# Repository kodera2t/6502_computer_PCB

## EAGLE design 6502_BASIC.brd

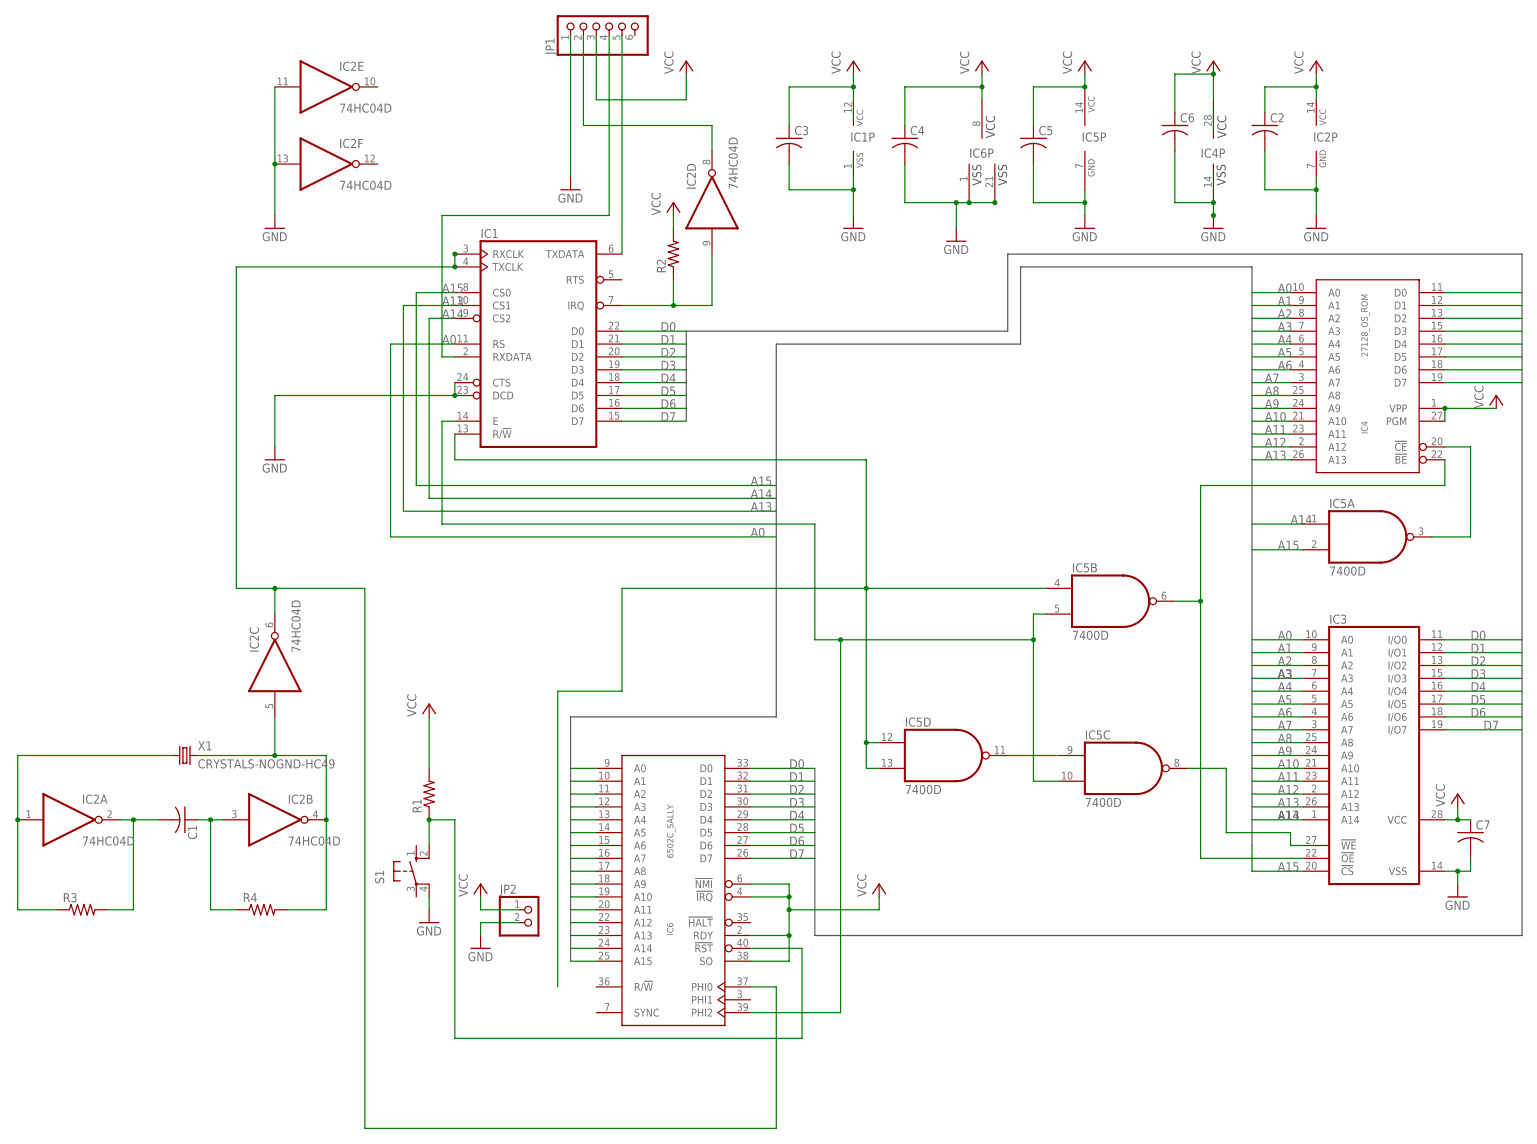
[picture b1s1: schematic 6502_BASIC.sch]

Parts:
C1, C2, C3, C4, C5, C6, C7: C-USC1608; C1608
IC1: 6850; DIL24
IC2: 74HC04D; SO14
IC3: 62256P; DIL28-6
IC4: 27128_OS_ROM; DIL28
IC5: 7400D; SO14
IC6: 6502C_SALLY; DIL40
JP1: HEADER-1X6; 1X06_OVAL
JP2: HEADER-1X2; 1X02_OVAL
R1, R2, R3, R4: R-US_R0603; R0603
S1: 10-XX; B3F-10XX
X1: CRYSTALS-NOGND-HC49; HC49

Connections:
A0: IC1.11 (RS), IC3.10 (A0), IC4.10 (A0), IC6.9 (A0)
A1: IC3.9 (A1), IC4.9 (A1), IC6.10 (A1)
A2: IC3.8 (A2), IC4.8 (A2), IC6.11 (A2)
A3: IC3.7 (A3), IC4.7 (A3), IC6.12 (A3)
A4: IC3.6 (A4), IC4.6 (A4), IC6.13 (A4)
A5: IC3.5 (A5), IC4.5 (A5), IC6.14 (A5)
A6: IC3.4 (A6), IC4.4 (A6), IC6.15 (A6)
A7: IC3.3 (A7), IC4.3 (A7), IC6.16 (A7)
A8: IC3.25 (A8), IC4.25 (A8), IC6.17 (A8)
A9: IC3.24 (A9), IC4.24 (A9), IC6.18 (A9)
A10: IC3.21 (A10), IC4.21 (A10), IC6.19 (A10)
A11: IC3.23 (A11), IC4.23 (A11), IC6.20 (A11)
A12: IC3.2 (A12), IC4.2 (A12), IC6.22 (A12)
A13: IC1.10 (CS1), IC3.26 (A13), IC4.26 (A13), IC6.23 (A13)
A14: IC1.9 (CS2), IC3.1 (A14), IC5.1 (I0), IC6.24 (A14)
A15: IC1.8 (CS0), IC3.20 (!CS), IC5.2 (I1), IC6.25 (A15)
D0: IC1.22 (D0), IC3.11 (I/O0), IC4.11 (D0), IC6.33 (D0)
D1: IC1.21 (D1), IC3.12 (I/O1), IC4.12 (D1), IC6.32 (D1)
D2: IC1.20 (D2), IC3.13 (I/O2), IC4.13 (D2), IC6.31 (D2)
D3: IC1.19 (D3), IC3.15 (I/O3), IC4.15 (D3), IC6.30 (D3)
D4: IC1.18 (D4), IC3.16 (I/O4), IC4.16 (D4), IC6.29 (D4)
D5: IC1.17 (D5), IC3.17 (I/O5), IC4.17 (D5), IC6.28 (D5)
D6: IC1.16 (D6), IC3.18 (I/O6), IC4.18 (D6), IC6.27 (D6)
D7: IC1.15 (D7), IC3.19 (I/O7), IC4.19 (D7), IC6.26 (D7)
GND: C2.2, C3.2, C4.2, C5.2, C6.2, C7.2, IC1.1 (VSS), IC1.23 (DCD), IC1.24 (CTS), IC2.7 (GND), IC2.11 (I), IC2.13 (I), IC3.14 (VSS), IC4.14 (VSS), IC5.7 (GND), IC6.1 (VSS), IC6.21 (VSS1), JP1.1, JP2.2, S1.4 (P1)
unnamed: IC3.27 (!WE), IC5.8 (O)
unnamed: IC3.22 (!OE), IC4.22 (!BE), IC5.6 (O)
unnamed: IC1.3 (RXCLK), IC1.4 (TXCLK), IC2.6 (O), IC6.37 (PHI0)
unnamed: IC5.9 (I0), IC5.11 (O)
unnamed: IC4.20 (!CE), IC5.3 (O)
unnamed: IC1.14 (E), IC5.5 (I1), IC5.10 (I1), IC6.39 (PHI2)
unnamed: IC1.13 (R/!W), IC5.4 (I0), IC5.12 (I0), IC5.13 (I1)
unnamed: IC2.4 (O), IC2.5 (I), R4.2, X1.2
unnamed: IC1.7 (IRQ), IC2.9 (I), R2.1
unnamed: IC2.8 (O), JP1.2
unnamed: C1.1, IC2.3 (I), R4.1
unnamed: IC6.40 (!RST), R1.1, S1.2 (S1)
unnamed: C1.2, IC2.2 (O), R3.2
unnamed: IC2.1 (I), R3.1, X1.1
unnamed: IC1.6 (TXDATA), JP1.5
unnamed: IC1.2 (RXDATA), JP1.4
VCC: C2.1, C3.1, C4.1, C5.1, C6.1, C7.1, IC1.12 (VCC), IC2.14 (VCC), IC3.28 (VCC), IC4.1 (VPP), IC4.27 (PGM), IC4.28 (VCC), IC5.14 (VCC), IC6.2 (RDY), IC6.4 (!IRQ), IC6.6 (!NMI), IC6.8 (VCC), IC6.38 (SO), JP1.3, JP2.1, R1.2, R2.2

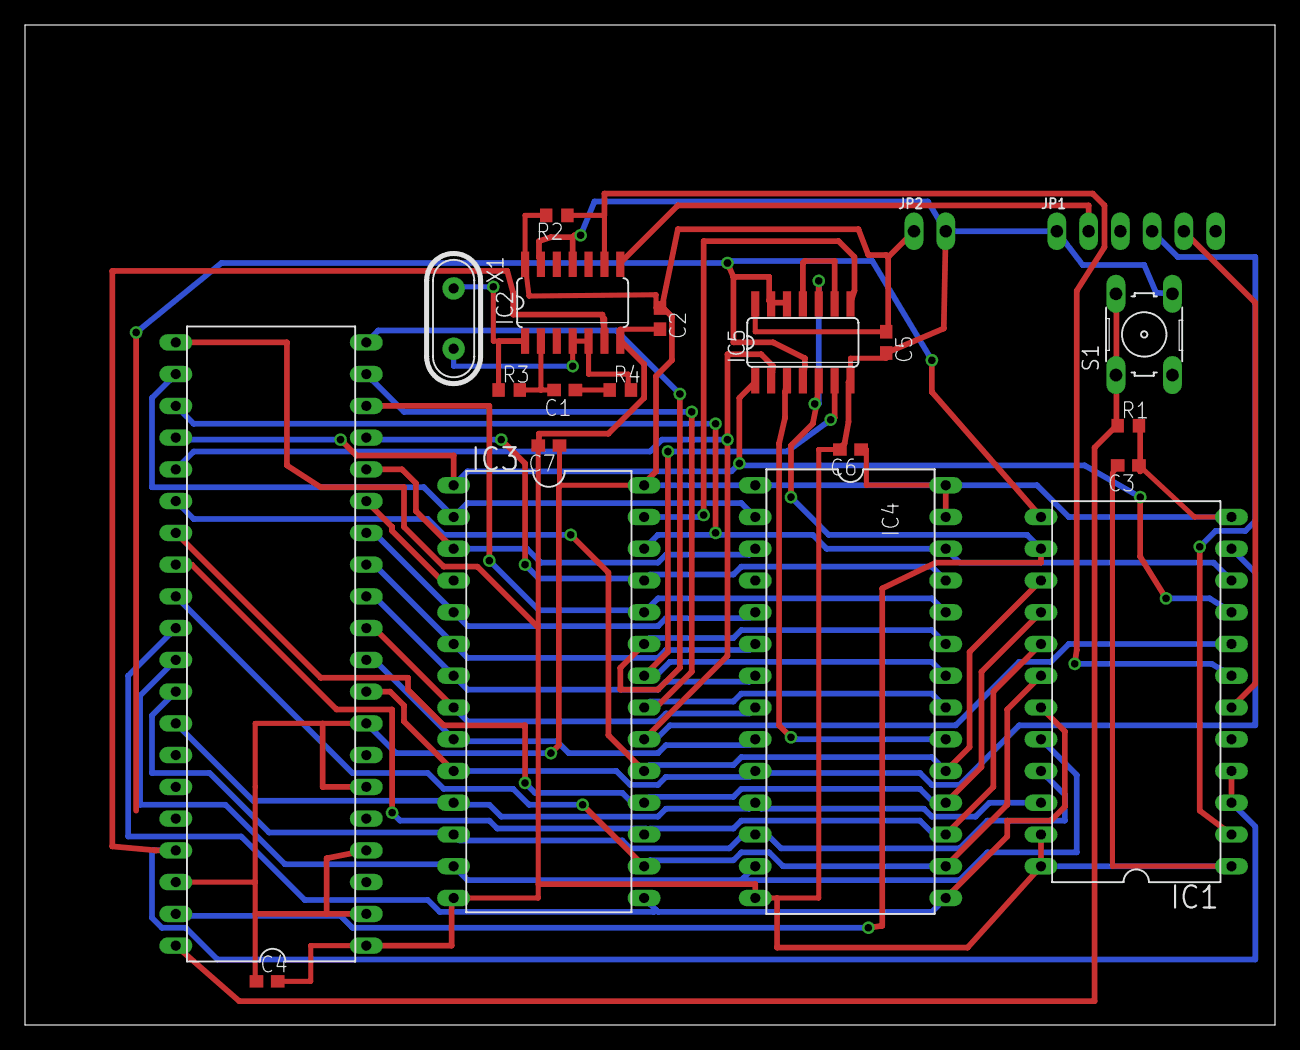
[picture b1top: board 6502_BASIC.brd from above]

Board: 2 copper layers, 100.0 x 80.0 mm, 21 parts (0 on the bottom side), 42 nets.

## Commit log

2015-12-05 initial submission

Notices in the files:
parts and their libraries:
eagle-6.5.0-atari: Copyright (c) 2010
Copyright (c) 2009
This library is licensed under the
Creative Commons Attribution 3.0 United States License.
OLED_mod: This work is placed in the public domain, and may be freely used for commercial and non-commercial work with the following conditions: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
